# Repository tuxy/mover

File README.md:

# Mover ROS2 Testbed (twenty-dollar project)

A small project to convert an old iRobot Essential into a ROS2 Testbed, with simple and cost-effective LiDAR-based navigation. No it isn't actually only twenty dollars, that's only the cost of the robot only, and because it rolls of the tongue nicely.

Structure:
 - `mover_controller`: closed-loop motor controller with a Pi Pico and the L298N (WIP)
 - `mover_pcb`: organised pcb for the pi pico, motors and motor-controller to interface nicely
 - `ros_ws`: workspace containing the packages & description for the robot.

## Parts (WIP)

| Part | Source | Cost (AUD) | Notes |
| ------------- | -------------- | -------------- | -------------- |
| Robot | Anywhere | $20 - $30 | |
| Raspberry Pi Pico | Anywhere | $5 - $10 | Should be the SMD version |
| PCB | JLCPCB | ~$11 | Includes shipping for 5pcs. Also includes the monthly deal |
| Terminal Blocks & Header pins | Jaycar | ~$12| 2x03 and 1x04 Terminal blocks and standard 40x headers to clip to size |
| Resistors (47k, 10k) | Jaycar | <$2 | |
| L298N | Jaycar / AliExpress |  $5 - $20 | |
| Raspberry Pi / Mini PC | Anywhere | $100 - $250 | Probably the most expensive part, if you replace the Pi Pico with a wireless one, it is possible to skip this and not use ROS |
| LiDAR Module (WitMotion D6) | AliExpress | $50 - $150 | Another really expensive part, this one could also be skipped if manual control via Pi Pico is preferred |
| Wires and Connectors | Anywhere | ~$20 | Really depends on how much soldering vs finding connectors. I opted to basically be completely non-intrusive and use stock connectors from the robot (JST ZH motor connectors) |

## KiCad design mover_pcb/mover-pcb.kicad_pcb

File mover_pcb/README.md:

# Simple PCB for organising controller work

Just a PCB to organise the controller, isn't necessary for functionality but definitely needed for sanity. Pi Pico symbol and footprint taken from Ki Lime Pi (https://github.com/recursivenomad/ki-lime-pi-to-go), otherwise the rest is default KiCAD 10.0.

(When I say 12V, I really mean the direct battery output, which ranges from ~13.0V to ~16.0V)

## Inputs 

The important part is the input, which are the top 3pin terminal block with 12V, GND and 5V, and the 4pin terminal block with MotorA and MotorB (the 4pin terminal could be direct-to-motor, but I opted for the board being the middle man). 

Also, the controller (should) be controlled through serial (USB).

## Outputs

The 12V, GND and 5V is directly outputted to the L298N driver board, as well as the:
 - Enable Pin A (MotorA's PWM Signal)
 - IN1 & IN2 Pins (MotorA's directional control)
 - Enable Pin B (MotorB's PWM Signal)
 - IN3 & IN4 Pins (MotorB's directional control)

The board also takes the 12V GND 5V input from the L298N and outputs it to the motor through the bottom 2x05 pin headers after getting the output from the L298N.

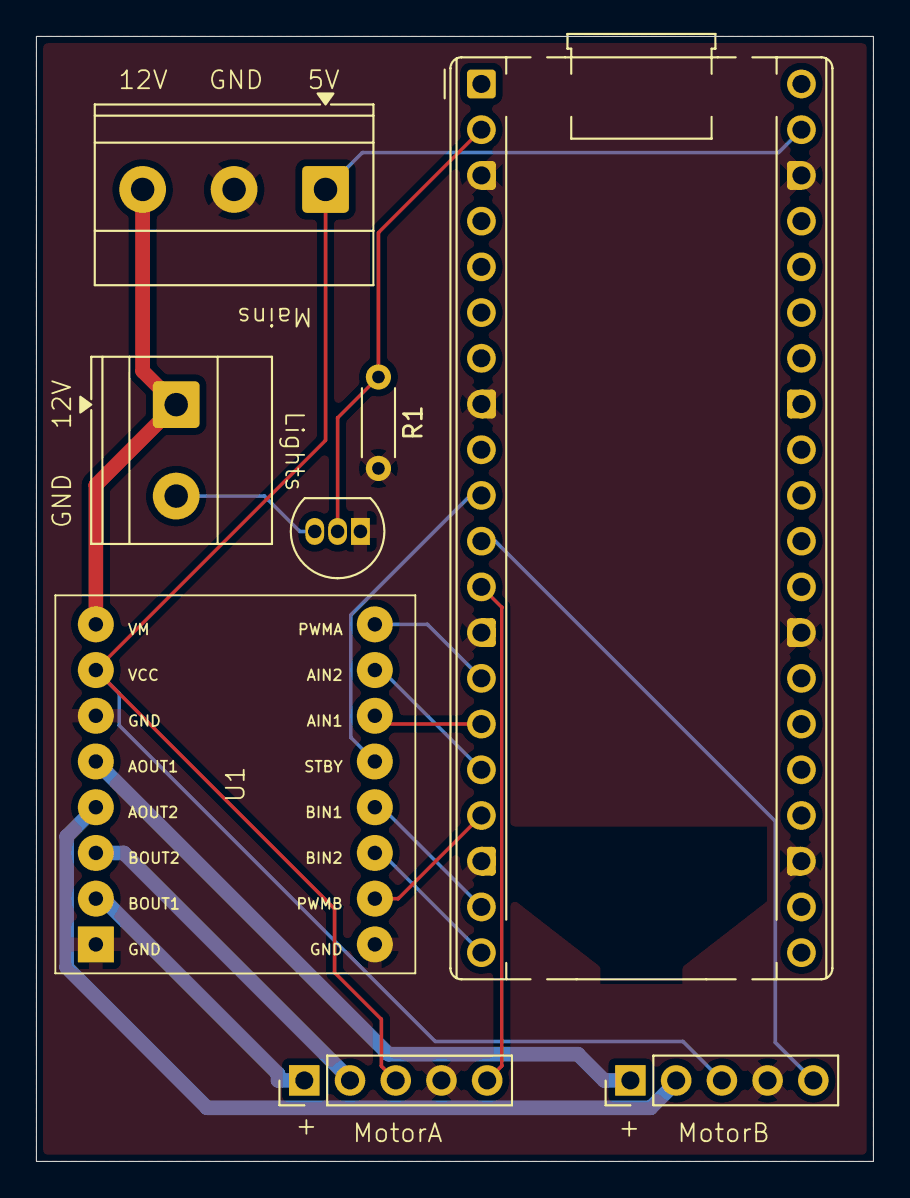
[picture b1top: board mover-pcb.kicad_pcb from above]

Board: 2 copper layers, 46.5 x 62.5 mm, 8 parts (0 on the bottom side), 18 nets.

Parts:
A1: RaspberryPi_Pico; RaspberryPi_Pico_Common_THT
J1: Conn_01x03_Pin; TerminalBlock_Phoenix_MKDS-1,5-3-5.08_1x03_P5.08mm_Horizont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
J2, J3: Conn_01x05_Pin; PinHeader_1x05_P2.54mm_Vertical
J4: Conn_01x02_Pin; TerminalBlock_Phoenix_MKDS-1,5-2-5.08_1x02_P5.08mm_Horizont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
Q2: BS170; TO-92_Inline
R1: 10k; R_Axial_DIN0204_L3.6mm_D1.6mm_P5.08mm_Horizontal
U1: TB6612FNG; TB6612FNG_Module

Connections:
5V: A1.39 (VSYS), J1.1, J2.3, J3.3, U1.20 (VCC)
12V: J1.3, J4.1, U1.24 (VM1)
Enable: A1.10 (GPIO7), U1.19 (STBY)
GND: A1.3 (GND), A1.8 (GND), A1.13 (GND), A1.18 (GND), A1.23 (GND), A1.28 (GND), A1.38 (GND), J1.2, J2.4, J3.4, Q2.1 (D), R1.2, U1.18 (GND)
H1L: A1.12 (GPIO9), J2.5
H1R: A1.11 (GPIO8), J3.5
IN1: A1.15 (GPIO11), U1.21 (AIN1)
IN2: A1.16 (GPIO12), U1.22 (AIN2)
IN3: A1.19 (GPIO14), U1.17 (BIN1)
IN4: A1.20 (GPIO15), U1.16 (BIN2)
Lights: A1.2 (GPIO1), Q2.2 (G), R1.1
MotorA+: J3.1, U1.1 (AO1)
MotorA-: J3.2, U1.5 (AO2)
MotorB+: J2.1, U1.11 (BO1)
MotorB-: J2.2, U1.7 (BO2)
unnamed: J4.2, Q2.3 (S)
PWMA: A1.14 (GPIO10), U1.23 (PWMA)
PWMB: A1.17 (GPIO13), U1.15 (PWMB)

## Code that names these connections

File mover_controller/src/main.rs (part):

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#[used]
static BOOT2: [u8; 256] = rp2040_boot2::BOOT_LOADER_GENERIC_03H;

type EncoderPinA = gpio::Pin<gpio::bank0::Gpio8, gpio::FunctionSioInput, gpio::PullUp>;
type EncoderPinB = gpio::Pin<gpio::bank0::Gpio9, gpio::FunctionSioInput, gpio::PullUp>;
type EncoderPins = (EncoderPinB, EncoderPinA);

static ENCODER_PINS: Mutex<RefCell<Option<EncoderPins>>> = Mutex::new(RefCell::new(None));
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fn main() -> ! {
    let mut system = System::init();

    let mut stby_pin = system.pins.gpio7.into_push_pull_output();
    stby_pin.set_high();

    // Steal PAC for peripherals consumed after System::init
    let mut pac = unsafe { hal::pac::Peripherals::steal() };

    // Encoder inputs
    let enc_a = system.pins.gpio9.into_pull_up_input();
    let enc_b = system.pins.gpio8.into_pull_up_input();

    enc_a.set_interrupt_enabled(gpio::Interrupt::EdgeHigh, true);
    enc_a.set_interrupt_enabled(gpio::Interrupt::EdgeLow, true);
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        motora_controller,
        pwm_slices.pwm6,
        channel_b,
        system.pins.gpio13,
        [
            system.pins.gpio14.into_push_pull_output(),
            system.pins.gpio15.into_push_pull_output()
        ]
    );

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        motorb_controller,
        pwm_slices.pwm5,
        channel_a,
        system.pins.gpio10,
        [
            system.pins.gpio11.into_push_pull_output(),
            system.pins.gpio12.into_push_pull_output()
        ]
    );

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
